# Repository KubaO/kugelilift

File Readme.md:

Kugelilift
==========

Check out the sources:

    git submodule update --init --recursive

To download EasyEDA/LCSC footprints and symbols on Windows, open the KiCad 8 command line prompt. Initialize it with

```
pip install easyeda2kicad
```

To download a symbol:

```
jlc --symbol --footprint --lcsc_id=C12345
```

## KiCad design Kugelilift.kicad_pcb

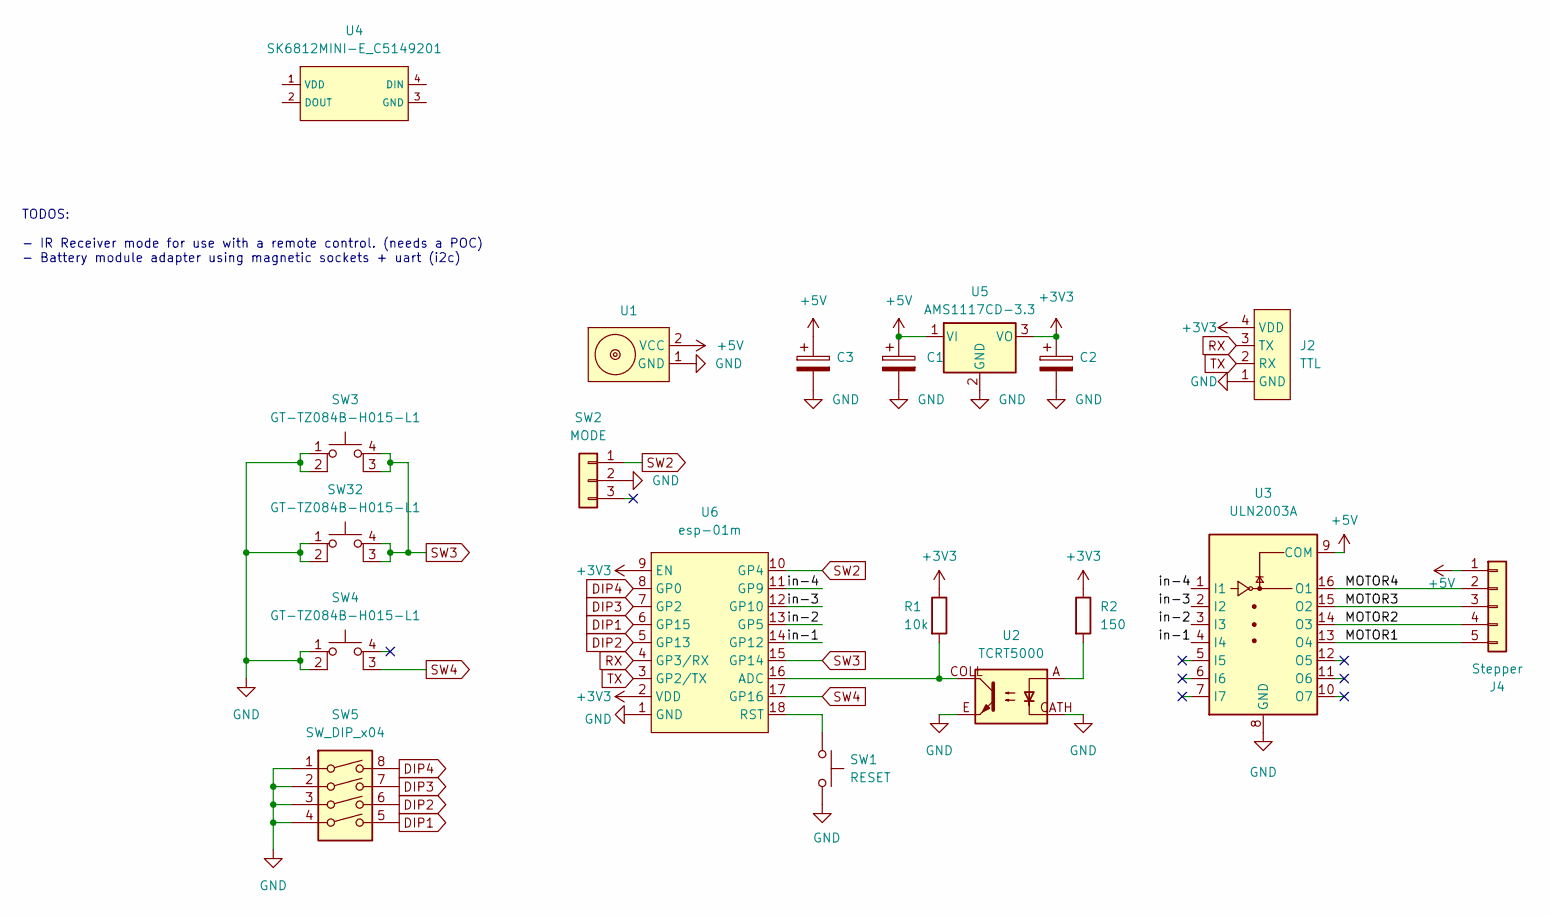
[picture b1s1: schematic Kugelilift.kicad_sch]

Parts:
C1, C2, C3: C_Polarized; CP_Radial_D6.3mm_P2.50mm
J2: TTL; PinHeader_1x04_P2.54mm_Vertical
J4: Stepper; JST_EH_B5B-EH-A_1x05_P2.50mm_Vertical
R1: 10k; R_Axial_DIN0207_L6.3mm_D2.5mm_P10.16mm_Horizontal
R2: 150; R_Axial_DIN0207_L6.3mm_D2.5mm_P7.62mm_Horizontal
SW1: RESET; PinHeader_1x03_P2.54mm_Vertical
SW2: MODE; PinHeader_1x03_P2.54mm_Vertical
SW3, SW4, SW32: GT-TZ084B-H015-L1; SW-SMD_4P-L5.2-W5.2-P3.70-LS6.4; LCSC C29780122
SW5: SW_DIP_x04; SW_DIP_SPSTx04_Slide_6.7x11.72mm_W7.62mm_P2.54mm_LowProfile
U1: magnetic-charger
U2: TCRT5000; tcrt5000
U3: ULN2003A; SOIC-16_3.9x9.9mm_P1.27mm
U4: SK6812MINI-E_C5149201; LED-SMD_L3.2-W2.8-LS5.9_SK6812MINI-E BACK; LCSC C5149201
U5: AMS1117CD-3.3; TO-252-2
U6: esp-01m

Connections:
+3V3: C2.1, J2.4 (VDD), R1.1, R2.1, U5.3 (VO), U6.2 (VDD), U6.9 (EN)
+5V: C1.1, C3.1, J4.1, U1.2 (VCC), U3.9 (COM), U5.1 (VI)
/MOTOR1: J4.5, U3.13 (O4)
/MOTOR2: J4.4, U3.14 (O3)
/MOTOR3: J4.3, U3.15 (O2)
/MOTOR4: J4.2, U3.16 (O1)
/in-1: U3.4 (I4), U6.14 (GP12)
/in-2: U3.3 (I3), U6.13 (GP5)
/in-3: U3.2 (I2), U6.12 (GP10)
/in-4: U3.1 (I1), U6.11 (GP9)
DIP1: SW5.5, U6.6 (GP15)
DIP2: SW5.6, U6.5 (GP13)
DIP3: SW5.7, U6.7 (GP2)
DIP4: SW5.8, U6.8 (GP0)
GND: C1.2, C2.2, C3.2, J2.1 (GND), SW1.2, SW2.2, SW3.1, SW3.2, SW4.1, SW4.2, SW5.1, SW5.2, SW5.3, SW5.4, SW32.1, SW32.2, U1.1 (GND), U2.CATH, U2.E, U3.8 (GND), U5.2 (GND), U6.1 (GND)
unnamed: R2.2, U2.A
unnamed: R1.2, U2.COLL, U6.16 (ADC)
unnamed: SW1.1, U6.18 (RST)
RX: J2.3 (TX), U6.4 (GP3/RX)
SW2: SW2.1, U6.10 (GP4)
SW3: SW3.3, SW3.4, SW32.3, SW32.4, U6.15 (GP14)
SW4: SW4.3, U6.17 (GP16)
TX: J2.2 (RX), U6.3 (GP2/TX)

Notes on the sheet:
TODOS: - IR Receiver mode for use with a remote control. (needs a POC) - Battery module adapter using magnetic sockets + uart (i2c)

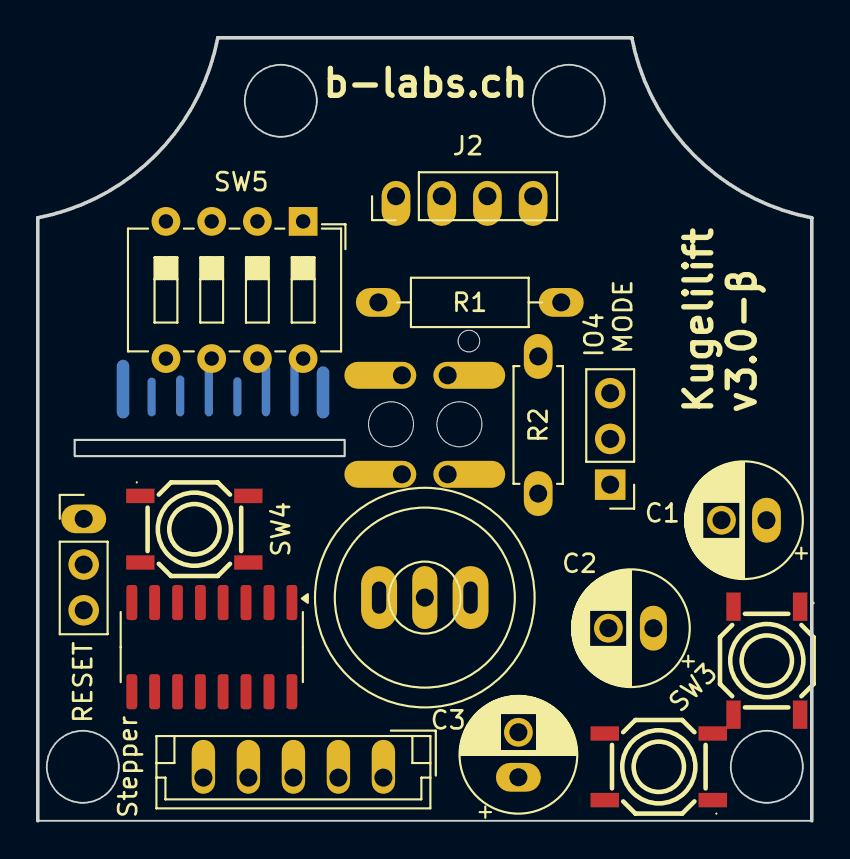
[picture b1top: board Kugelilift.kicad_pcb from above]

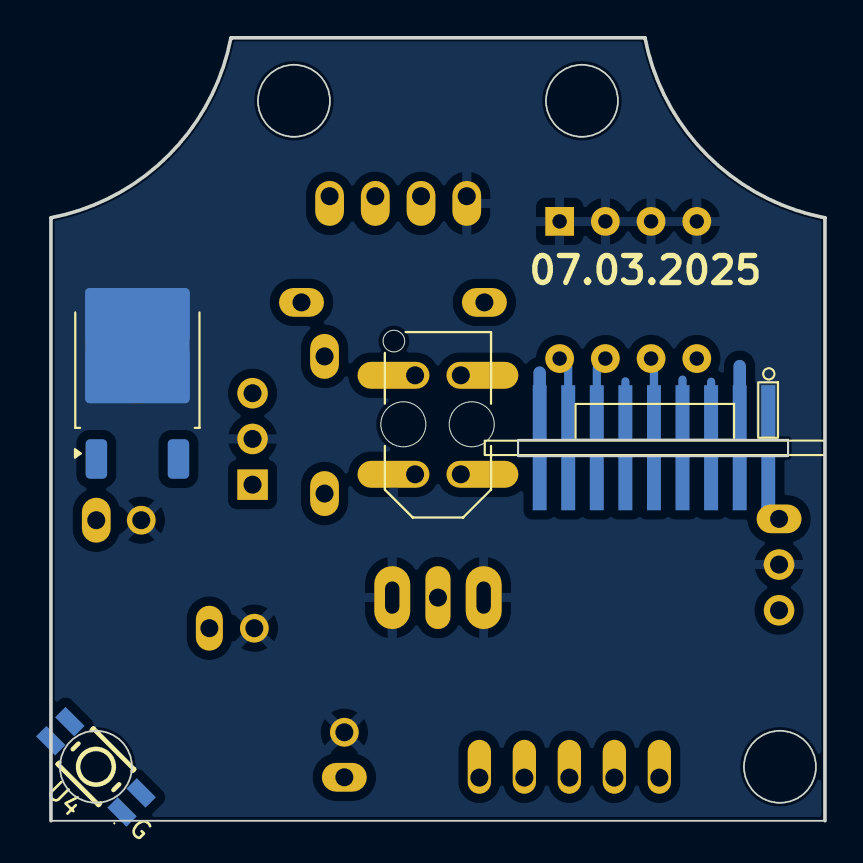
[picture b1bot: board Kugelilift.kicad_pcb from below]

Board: 2 copper layers, 43.0 x 43.5 mm, 19 parts (4 on the bottom side), 23 nets.

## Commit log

2025-03-07 Laid out pushbuttons and dip switches
2025-03-12 Add LCSC/JLC download script for Windows.
2025-03-12 Add the switch symbol
2025-03-12 Update to "hard" pushbuttons, rearrange components.
2025-03-17 Rearrange components.
2025-03-17 Add the LED footprint.
2025-03-17 Use the LED footprint.
